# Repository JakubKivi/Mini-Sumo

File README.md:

# Mini-Sumo
First really project by CałkaCompany+

Oznaczenia wyjść i wejść w kodzie:

| numer wyjścia | arduino | zmienna w kodzie  |                 opis            |
| ------------  |---------| ----------------  | ------------------------------  |
|       1       |  PWM/D11 |      `floorBR`    |    Czujnik podłoża prawy tylny  |
|       2       |    D13   |      `floorFR`    |   Czujnik podłoża prawy przedni |
|      31       |  D10  |     `floorBL`     |   Czujnik podłoża lewy tylny    |
|      32       |    D12   |     `floorFL`     |  Czujnik podłoża lewy przedni   |
|               |         |                   |                                 |
|    3\5\21     |   GND   |         `-`       |           Uziemienie            |
|      4\6      |   VCC   |         `-`       |           Zasilanie             |
|               |         |                   |                                 |
|      ?        |    D12  |       `AIN1`      |       Prawy silnik w tył        |\
|       ?       |    D13  |       `AIN2`      |      Prawy silnik w przód       | \    Patrząc na
|      ?        |    D10  |       `BIN1`      |       Lewy silnik  w tył        | /      mordke!
|       ?       |    D11  |       `BIN2`      |      Lewy silnik  w przód       |/
|               |         |                   |                                 |
|      ?        |    D3   |      `sensorFL`   | Czujnik odległości lewy przedni |
|      ?        |    D2   |     `sensorFR`    | Czujnik odległości prawy przedni|
|      ?        |    D0   |     `sensorF`     |   Czujnik odległości przedni    |
|      ?        |    D1   |     `sensorBL`    | Czujnik odległości prawy tylny  |
|      ?        |    D7   |     `sensorB`     |   Czujnik odległości tylni      |
|      ?        |    D4   |     `sensorBR`    |  Czujnik odległości prawy tylni |

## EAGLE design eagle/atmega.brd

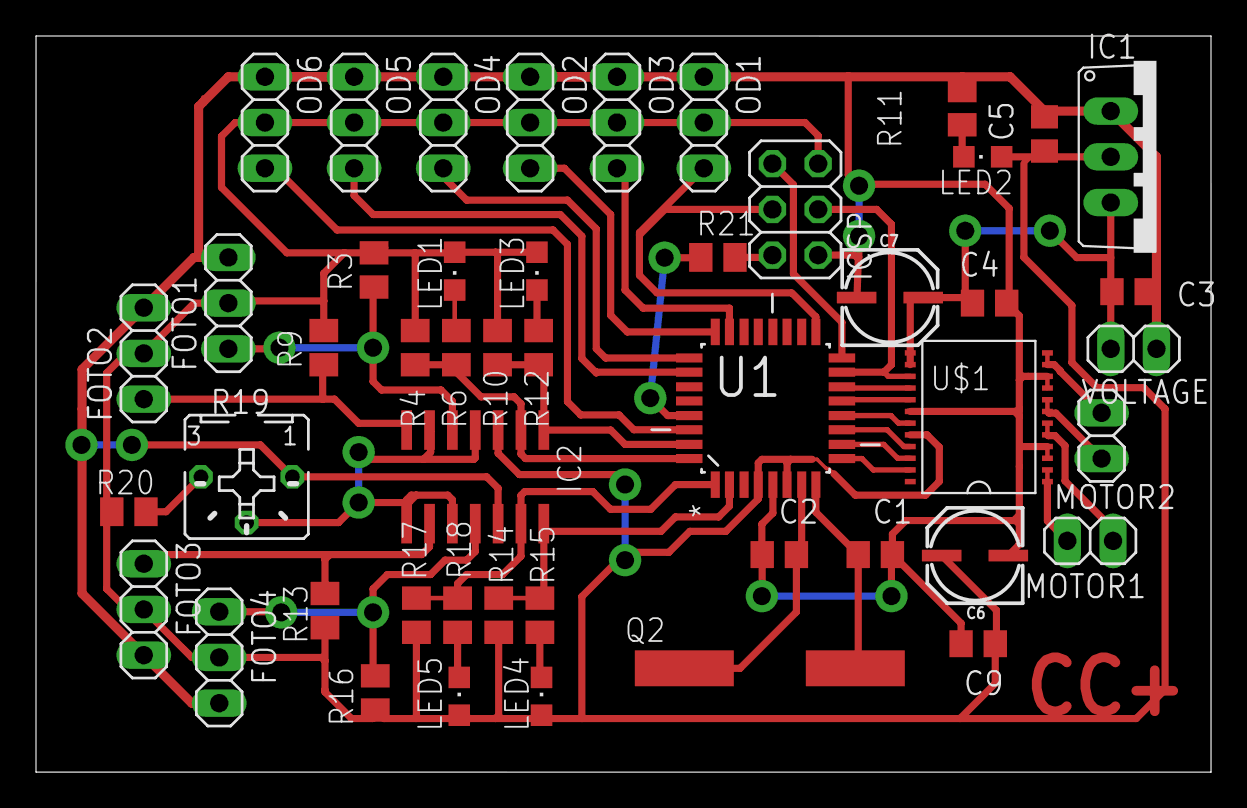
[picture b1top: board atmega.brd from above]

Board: 2 copper layers, 65.3 x 40.9 mm, 48 parts (0 on the bottom side), 40 nets.

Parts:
C1, C2: 22pF; C0805
C3: 220nF; C0805
C4, C5, C9: 100nF; C0805
C6, C7: 10uF; PANASONIC_C
FOTO1, FOTO2, FOTO3, FOTO4: 1X03
IC1: TO 5V; TO220V
IC2: LM339D; SO14
ICSP: 2X03
LED1, LED2, LED3, LED4, LED5: CHIPLED_0805
MOTOR1, MOTOR2: 1X02
OD1, OD2, OD3, OD4, OD5, OD6: 1X03
Q2: 16MHz; CSM-7X-DU
R3, R9, R13, R16: 22k; M0805
R4, R10, R14, R17: 100k; M0805
R6, R11, R12, R15, R18: 220R; M0805
R19: B25P
R20: 2.2k; M0805
R21: 10k; M0805
U1: ATMEGA328P-AU; QFP80P900X900X120-32N
U$1: TB6612FNG; SSOP24
VOLTAGE: 1X02

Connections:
AIN1: U1.11, U$1.21
AIN2: U1.10, U$1.22
BIN1: U1.13, U$1.17
BIN2: U1.14, U$1.16
CO1: ICSP.3, OD1.3, U1.17
CO2: OD2.3, U1.24
CO3: OD3.3, U1.23
CO4: OD4.3, U1.25
CO5: OD5.3, U1.26
CO6: OD6.3, U1.30
GND: C1.1, C2.1, C3.1, C4.1, C5.1, C6.-, C7.-, C9.1, FOTO1.3, FOTO2.3, FOTO3.3, FOTO4.3, IC1.1, IC2.12, ICSP.6, OD1.1, OD2.1, OD3.1, OD4.1, OD5.1, OD6.1, R11.1, R19.A, U1.5, U$1.3, U$1.4, U$1.9, U$1.10, U$1.18, VOLTAGE.2
KO1: IC2.2, R4.1, R6.1, U1.32
KO2: IC2.1, R10.1, R12.1, U1.31
KO3: IC2.14, R14.1, R15.1, U1.2
KO4: IC2.13, R17.1, R18.1, U1.1
KOM1: FOTO1.1, IC2.5, R3.1
KOM2: FOTO2.1, IC2.7, R9.1
KOM3: FOTO3.1, IC2.9, R13.1
KOM4: FOTO4.1, IC2.11, R16.1
KWARC1: C2.2, Q2.1, U1.7
KWARC2: C1.2, Q2.2, U1.8
unnamed: LED3.C, R12.2
unnamed: R19.E, R20.1
unnamed: LED2.C, R11.2
unnamed: LED1.C, R6.2
unnamed: LED4.C, R15.2
unnamed: LED5.C, R18.2
OUTMA1: MOTOR1.2, U$1.1, U$1.2
OUTMA2: MOTOR1.1, U$1.5, U$1.6
OUTMB1: MOTOR2.1, U$1.11, U$1.12
OUTMB2: MOTOR2.2, U$1.7, U$1.8
POT: IC2.4, IC2.6, IC2.8, IC2.10, R19.S
PROG: ICSP.1, U1.16
PWMA: U1.9, U$1.23
PWMB: ICSP.4, U1.15, U$1.15
RESET: ICSP.5, R21.2
RESET1: R21.1, U1.29
STBY: U1.12, U$1.19
VCC: C5.2, C6.+, C9.2, FOTO1.2, FOTO2.2, FOTO3.2, FOTO4.2, IC1.2, IC2.3, ICSP.2, LED1.A, LED2.A, LED3.A, LED4.A, LED5.A, OD1.2, OD2.2, OD3.2, OD4.2, OD5.2, OD6.2, R3.2, R4.2, R9.2, R10.2, R13.2, R14.2, R16.2, R17.2, R20.2, U1.4, U1.6, U$1.20
VZ: C3.2, C4.2, C7.+, IC1.3, U$1.13, U$1.14, VOLTAGE.1

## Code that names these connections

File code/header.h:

//floor sensor
#define floorFL  	//front left 
#define floorFR		//front right
#define floorBL		//back
#define floorBR
//distance sensor front
#define sensorF 	
#define sensorFL
#define sensorFR
#define sensorB
#define sensorBL
#define sensorBR

//motor
#define AIN1
#define AIN2
#define BIN1
#define	BIN2
#define PWMA
#define PWMB
#define STBY



bool direction = true;
int speed; 
bool touchFloor; 					//czy dotyka podłogi
bool seeEnemy;						//czy widzi przeciwnika
void toSeeEnemyFront(speed);		//zrób tak żeby przeciwnik był nawprost
void go(bool direction, speed); 	//jedź just jedź				jak pobrać zmienną globalną???





//sterowanie silnika
void goFoward(int speed);
void goFowardLeft(int speed);
void goFowardRight(int speed);
void goBackword(int speed);
void goBackwordLeft(int speed);
void goBackwordRight(int speed);
void stop(bool direction); //zatrzymywanie się tyłem przodem???? jest jakaś różnica?

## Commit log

2018-02-04 Początek projektu płytki PCB.
2018-02-04 Dodany plik README.md
2018-02-06 Stworzenie readme
2018-02-06 Lista zakupów publiczna
2018-02-06 Ładniej wygląda, dodałem transobtor zamiast fotorezystorów. Podłączenie komparatorów
2018-02-06 zmiana pinów ICSP (programowanie) z 6x1 na 2x3
2018-02-06 zmiana pinów wychodzący (silniki) piny na czujniki, skończone podłączanie elementów.
2018-02-07 Zmiany podłączenia. Rozpoczęgie pracy nad płyką PCB.
2018-02-08 Przygotowywanie do zmiany procesora.
2018-02-09 Dodanie arkusza z listą zakupów.
2018-02-09 Dodanie mini USB. Dodaj rezystory przed USB, podmień obudowy rezystorów.
2018-02-10 Arkusz nieskończony
    aha
2018-02-10 Dodano zużycie do kondensatorów
2018-02-11 Podłączenie USB, Początek podłączania do sterownika.
2018-02-11 do sprawdzenia czy wszystko dobrze
2018-02-11 Podłączone USB, ale nie wiem jak podłączyć tego procka...
2018-02-11 Usunąłem ATmega32U
2018-02-11 ostateczne sprawdzenie' git push origin master git status
2018-02-11 Podłączenie wszystkiego zakończone, wystarczy tylko obawić się nad estetyką
2018-02-11 Zdjęcie do wydruku ostatnie poprawki (jedna ścieżka nie była podłączona), zdjęcie nie w formacie A4
2018-02-11 Format A4
2018-02-13 zapomiałem co się działo
2018-02-13 Dodano pliki do wydruku i podglądu
2018-02-25 Zabawa Blenderem że aż mi się ostrza stępiły
2018-02-28 pierwszy kommit
2018-03-01 poprawnienie płytki
2018-03-04 dodano rysunek techniczny
2018-03-07 Do wydruku wszystko
2018-03-07 Dodano napis na pcb
2018-03-18 Gotowa do wysyłki
2018-03-22 Pogrubienie ścieżek
2018-03-23 Poprawienie przelotek
2018-03-28 Przelotkę w końcu zrobiłem dobrze ale muszę dokończyć
    na infie
2018-03-28 Ogrubienie przelotek
2018-03-29 Usunięcie zwarć
2018-03-29 Przesunięcie napisu ze ścierzek
2018-03-29 Usunięcie śmietnika i dodanie napisu
2018-03-29 Napraawiłem
2018-04-04 Started coding
    Pisanie kodu do naszego robota.
2018-04-04 Ostateczne oddanie płytki
2018-04-04 Dodano pinMode() dla czujników odległości
2018-04-04 Przeniesienie pliku sumo.cpp do katalogu code
2018-04-04 toSeeEnemyFront() kilka dodatków
2018-04-04 Wzrór porogramu
2018-04-04 Dodałem body.cpp i header.h żeby lepiej się patrzyło
2018-04-04 Uporządkowanie kodu
2018-04-04 Porządkowanie
2018-04-04 Dodanie silnika
2018-04-05 Fixing Delis firs program :v
2018-04-05 Przeniesienie #definow do header.h
2018-04-05 Wszystko co dobre i dziala
2018-04-05 Poprawiony commit
2018-04-05 usuniecie Smieci
2018-04-05 eagle/eagle.epf to jednak nie śmietk xD
2018-04-05 Naprawianie kodu do stanu kompilowalnego
2018-04-05 Wypełniono tabelkę
2018-04-05 Dopisanie kilku komentarzy do schematu
2018-04-05 sprątanie syfu deliego i już nawet działa tylko napisać funkcje
2018-04-06 Wypełnienie wszystkich funkcji, poza outOfLine()
2018-04-06 Szybki commit dla deliego
2018-04-06 Wszstko gotowe do testów
2018-04-06 Przypisanie pinom odpowiednich nazw
2018-04-07 Uporządkowanie kolejności funkcji w header.h
2018-04-07 Drobne zmiany funkcji i zmiennych, na wersje arduino
2018-04-13 Dodanie komentarzy
2018-04-14 usunięcie LEDów
2018-04-14 usunięcie starej płytki
2018-04-15 Dodano zasilanie, ISCP, podłączono do tego atmege
2018-04-15 komparator
2018-04-18 zmieny projektu
2018-04-20 Zmiana pinów na płytkę Kiviego
2018-04-20 Poprawka do poprzedniego usunięcie STBY
2018-04-23 Dodanie działającego kodu z festiwalu
2019-04-26 dodano .gitignore
2019-04-26 dodano platformoi.ini do .gitignore
2019-04-26 zmiana IDE na platformio i outputs na festiwalu 2019
2019-04-27 zmiana pinow od silnikow
2019-05-11 silniki gotowe śmigają równolegle!
2019-05-11 piny wszystkie so tak jak powinny
2019-05-11 usuniecie syfu
2019-05-11 gitignore
2019-05-12 spinuje i widzi z fronu
2019-05-12 taki co patrzy tlko przodami ale szypko
2019-05-12 zasuwa za reką najprostrzy program ever ale dziala
2019-05-12 przygotowany do patrzenia pod nogi :P
2019-05-12 mini popraweczka na while
2019-05-12 gotowy, wystarczy usunac komentarze przy sprawdzaniu pod nogi

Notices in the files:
parts and their libraries:
SparkFun-Capacitors: Licensing: Creative Commons ShareAlike 4.0 International - https://creativecommons.org/licenses/by-sa/4.0
